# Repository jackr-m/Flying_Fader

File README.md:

# Flying Faders
## Use Rust Embassy framework to integrate 5 "flying faders" (motorized linear slide potentiometers) as a USB MIDI CC controller

- [Flying Faders](#flying-faders)
   * [Use Rust Embassy framework to integrate 5 "flying faders" (motorized linear slide potentiometers) as a USB MIDI CC controller](#use-rust-embassy-framework-to-integrate-5-flying-faders-motorized-linear-slide-potentiometers-as-a-usb-midi-cc-controller)
   * [Project Overview](#project-overview)
      + [Code](#code)
      + [Mechanical](#mechanical)

## Project Overview
Use 5 motorized linear slide potentiometers (ALPS SM10002NKA1X-HW1, sold as Adafruit P/N 5466) with a STM32H7 microprocessor programmed using the Rust Embassy framework & HAL.
There is a custom PCB for this project, with the KiCad source in the /CAD directory.

### Code
Using the Rust Embassy framework and embassy_stm32 HAL, this has been coded using an asynchronous architecture and should be very portable to nearly any STM32 variant (especially if the screen is not needed).
Code documentation located at: https://jackr-m.github.io/Flying_Fader/flying_fader/

### Mechanical
The casement is 3D printed, and STEP files are provided in the /CAD directory.
In addition, the original Onshape document is available for use or modification at [Onshape](https://cad.onshape.com/documents/5790ae0e6f82956a005dc546/w/d37346e9ef2c1592c912aa6b/e/dacfcc9dc0c38682bf8baa7f?renderMode=0&uiState=666d3492034c5f73c5a59cf9).

Faders:

https://www.adafruit.com/product/5466

Screen:

https://www.adafruit.com/product/5805

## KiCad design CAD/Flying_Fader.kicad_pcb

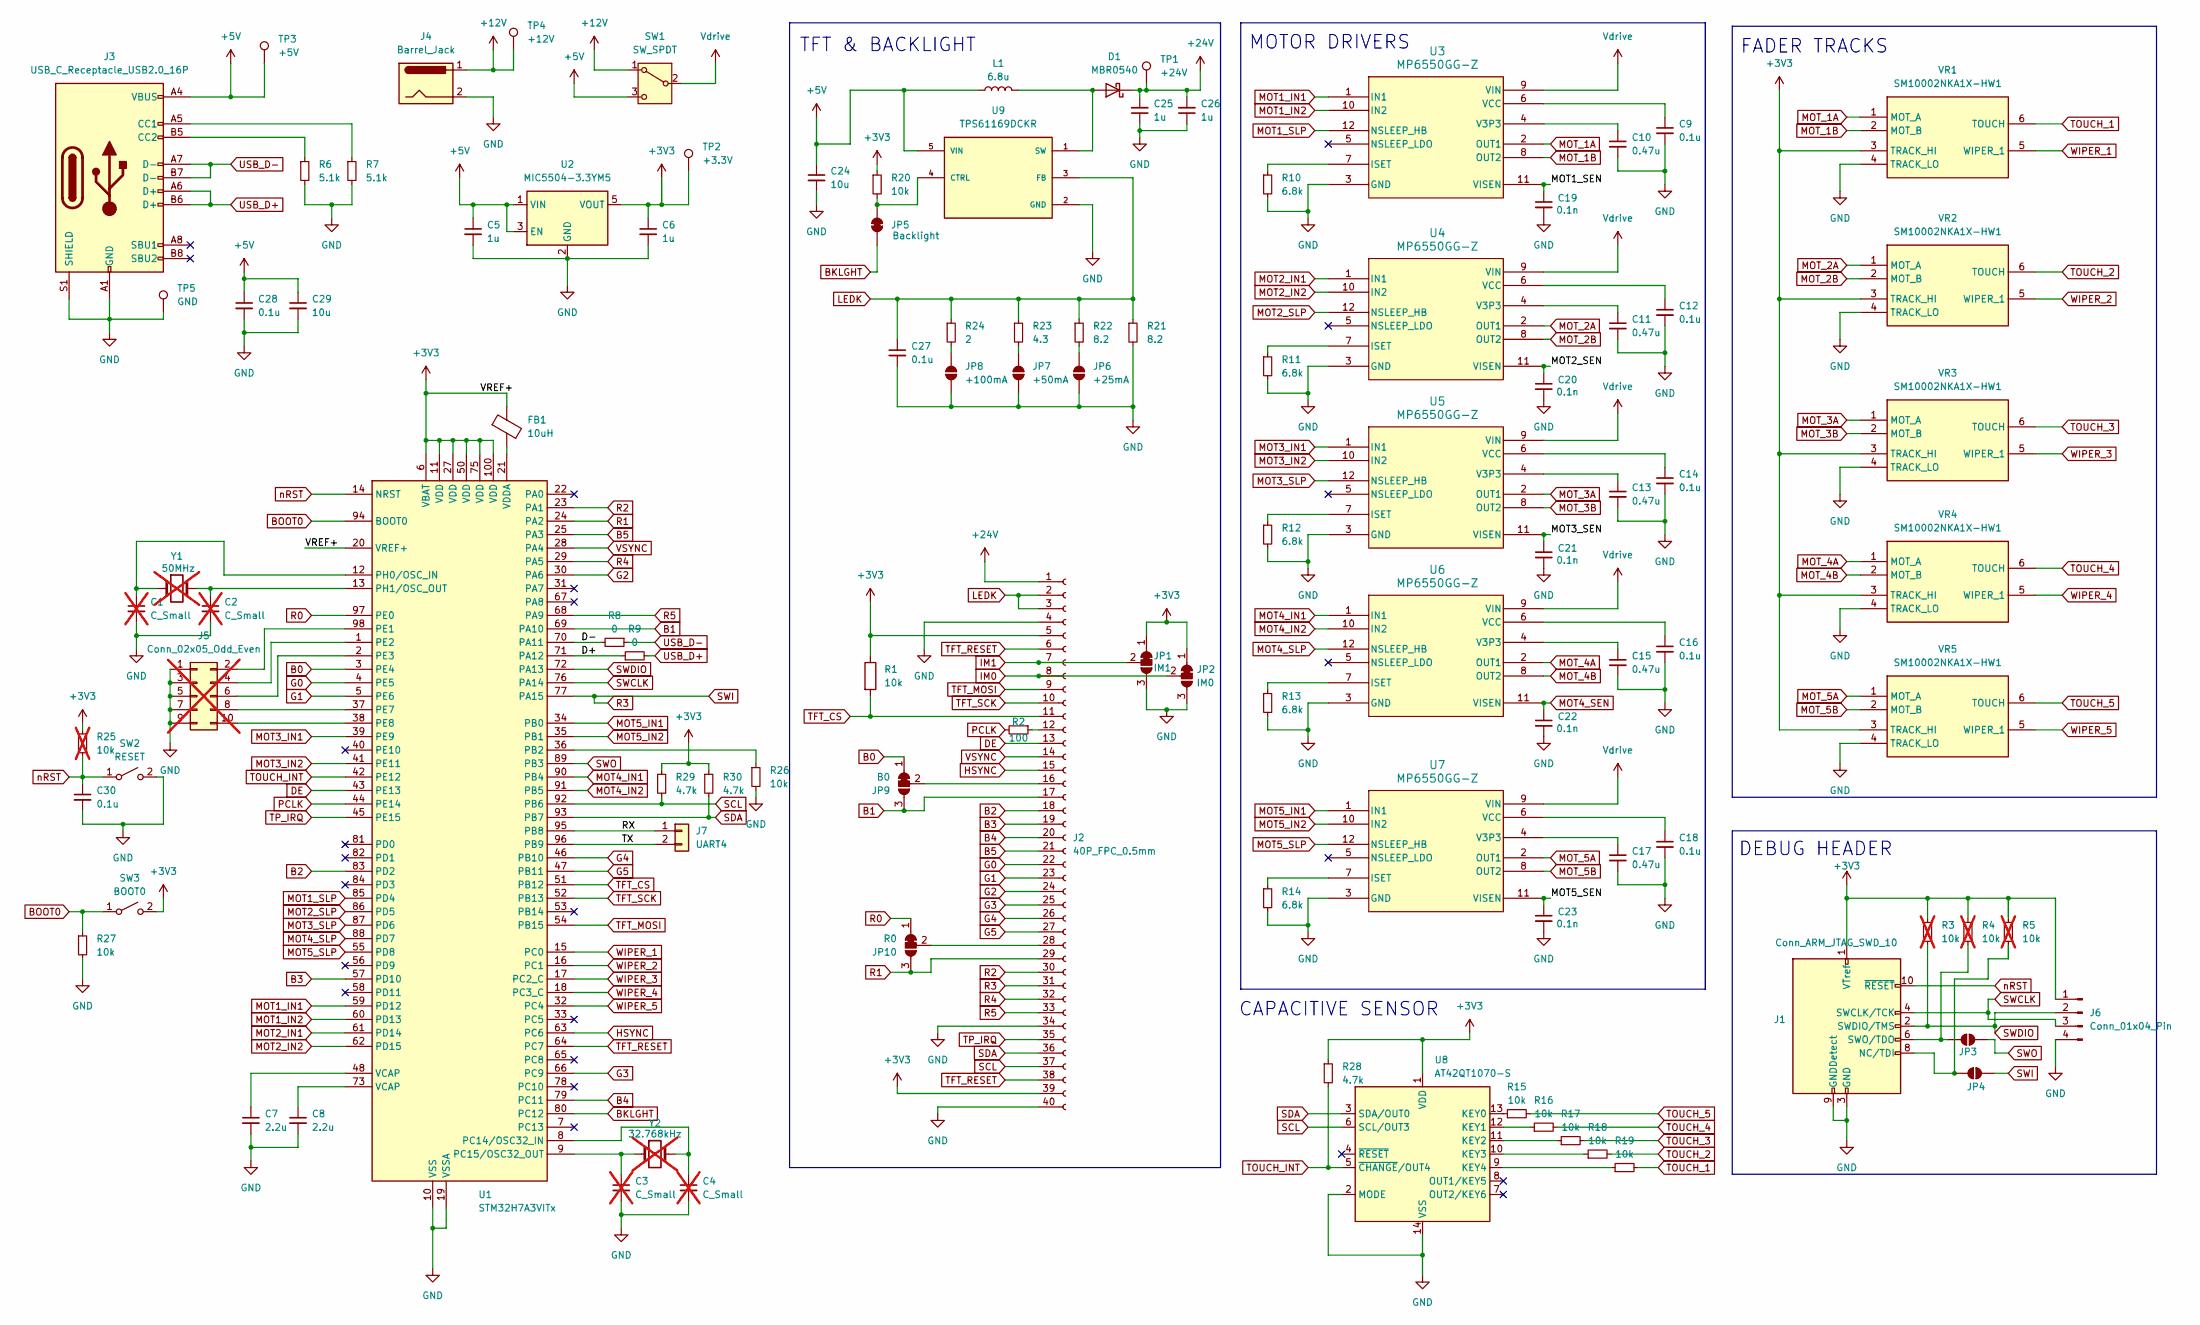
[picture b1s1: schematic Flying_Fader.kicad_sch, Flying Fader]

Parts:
C1, C2, C3, C4: C_Small; C_0805_2012Metric; not fitted
C5, C6, C25, C26: 1u; C_0805_2012Metric
C7, C8: 2.2u; C_0805_2012Metric
C9, C12, C14, C16, C18, C27, C28, C30: 0.1u; C_0805_2012Metric
C10, C11, C13, C15, C17: 0.47u; C_0805_2012Metric
C19, C20, C21, C22, C23: 0.1n; C_0805_2012Metric
C24, C29: 10u; C_0805_2012Metric
D1: MBR0540; D_SOD-123
FB1: 10uH; L_0805_2012Metric
J1: Conn_ARM_JTAG_SWD_10; PinHeader_2x05_P1.27mm_Vertical_SMD
J2: 40P_FPC_0.5mm; Omron_XF2M-4015-1A_1x40-1MP_P0.5mm_Horizontal
J3: USB_C_Receptacle_USB2.0_16P; USB_C_Receptacle_GCT_USB4085
J4: Barrel_Jack; BarrelJack_CUI_PJ-063AH_Horizontal
J5: Conn_02x05_Odd_Even; PinHeader_2x05_P2.54mm_Vertical; not fitted
J6: Conn_01x04_Pin; PinHeader_1x04_P2.54mm_Vertical
J7: UART4; PinHeader_1x02_P2.54mm_Vertical
JP1: IM1; SolderJumper-3_P1.3mm_Bridged12_Pad1.0x1.5mm_NumberLabels
JP2: IM0; SolderJumper-3_P1.3mm_Bridged12_Pad1.0x1.5mm_NumberLabels
JP3: SWO; SolderJumper-2_P1.3mm_Open_TrianglePad1.0x1.5mm
JP4: SWI; SolderJumper-2_P1.3mm_Open_TrianglePad1.0x1.5mm
JP5: Backlight; SolderJumper-2_P1.3mm_Bridged_Pad1.0x1.5mm
JP6: +25mA; SolderJumper-2_P1.3mm_Open_TrianglePad1.0x1.5mm
JP7: +50mA; SolderJumper-2_P1.3mm_Open_TrianglePad1.0x1.5mm
JP8: +100mA; SolderJumper-2_P1.3mm_Open_TrianglePad1.0x1.5mm
JP9: B0; SolderJumper-3_P1.3mm_Bridged12_Pad1.0x1.5mm_NumberLabels
JP10: R0; SolderJumper-3_P1.3mm_Bridged12_Pad1.0x1.5mm_NumberLabels
L1: 6.8u; L_0805_2012Metric
R1, R15, R16, R17, R18, R19, R20, R26, R27: 10k; R_0805_2012Metric
R2: 100; R_0805_2012Metric
R3, R4, R5, R25: 10k; R_0805_2012Metric; not fitted
R6, R7: 5.1k; R_0805_2012Metric
R8, R9: 0; R_0805_2012Metric
R10, R11, R12, R13, R14: 6.8k; R_0805_2012Metric
R21, R22: 8.2; R_0805_2012Metric
R23: 4.3; R_0805_2012Metric
R24: 2; R_0805_2012Metric
R28, R29, R30: 4.7k; R_0805_2012Metric
SW1: SW_SPDT; SW_SPDT_CK_JS102011SAQN
SW2: RESET; SW_Push_SPST_NO_Alps_SKRK
SW3: BOOT0; SW_Push_SPST_NO_Alps_SKRK
TP1: +24V; TestPoint_Pad_D1.0mm
TP2: +3.3V; TestPoint_Pad_D1.0mm
TP3: +5V; TestPoint_Pad_D1.0mm
TP4: +12V; TestPoint_Pad_D1.0mm
TP5: GND; TestPoint_Pad_D1.0mm
U1: STM32H7A3VITx; LQFP-100_14x14mm_P0.5mm
U2: MIC5504-3.3YM5; SOT-23-5
U3, U4, U5, U6, U7: MP6550GG-Z; LQFN-12-1EP_2x2mm_P0.5mm_EP0.7x0.7mm
U8: AT42QT1070-S; SOIC-14_3.9x8.7mm_P1.27mm
U9: TPS61169DCKR; SOT-353_SC-70-5; PARTREV A
VR1, VR2, VR3, VR4, VR5: SM10002NKA1X-HW1; PinHeader_1x06_P2.54mm_Vertical; Manufacturer_Part_Number SM10002NKA1X-HW1
Y1: 50MHz; Crystal_SMD_5032-2Pin_5.0x3.2mm; not fitted
Y2: 32.768kHz; Crystal_SMD_3215-2Pin_3.2x1.5mm; not fitted

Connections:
+3V3: C6.1, FB1.1, J1.1 (VTref), J2.5, J2.39, J6.1, JP1.1 (A), JP2.1 (A), R1.1, R3.1, R4.1, R5.1, R20.1, R25.1, R28.1, R29.1, R30.1, SW3.2 (B), TP2.1, U1.6 (VBAT), U1.11 (VDD), U1.20 (VREF+), U1.27 (VDD), U1.50 (VDD), U1.75 (VDD), U1.100 (VDD), U2.5 (VOUT), U8.1 (VDD), VR1.3 (TRACK_HI), VR2.3 (TRACK_HI), VR3.3 (TRACK_HI), VR4.3 (TRACK_HI), VR5.3 (TRACK_HI)
+5V: C5.1, C24.1, C28.1, C29.1, J3.A4 (VBUS), J3.A9 (VBUS), J3.B4 (VBUS), J3.B9 (VBUS), L1.1, SW1.3 (C), TP3.1, U2.1 (VIN), U2.3 (EN), U9.5 (VIN)
+12V: J4.1, SW1.1 (A), TP4.1
+24V: C25.2, C26.2, D1.1 (K), J2.1, TP1.1
/D+: R9.1, U1.71 (PA12)
/D-: R8.2, U1.70 (PA11)
/MOT1_SEN: C19.1, U3.11 (VISEN)
/MOT2_SEN: C20.1, U4.11 (VISEN)
/MOT3_SEN: C21.1, U5.11 (VISEN)
/MOT5_SEN: C23.1, U7.11 (VISEN)
/RX: J7.1, U1.95 (PB8)
/TX: J7.2, U1.96 (PB9)
B0: JP9.1 (A), U1.3 (PE4)
B1: J2.17, JP9.3 (B), U1.69 (PA10)
B2: J2.18, U1.83 (PD2)
B3: J2.19, U1.57 (PD10)
B4: J2.20, U1.79 (PC11)
B5: J2.21, U1.25 (PA3)
BKLGHT: JP5.1 (A), U1.80 (PC12)
BOOT0: R27.1, SW3.1 (A), U1.94 (BOOT0)
DE: J2.13, U1.43 (PE13)
G0: J2.22, U1.4 (PE5)
G1: J2.23, U1.5 (PE6)
G2: J2.24, U1.30 (PA6)
G3: J2.25, U1.66 (PC9)
G4: J2.26, U1.46 (PB10)
G5: J2.27, U1.47 (PB11)
GND: C1.2, C2.2, C3.2, C4.2, C5.2, C6.2, C7.2, C8.2, C9.2, C10.2, C11.2, C12.2, C13.2, C14.2, C15.2, C16.2, C17.2, C18.2, C19.2, C20.2, C21.2, C22.2, C23.2, C24.2, C25.1, C26.1, C27.2, C28.2, C29.2, C30.2, J1.3 (GND), J1.5 (GND), J1.9 (GNDDetect), J2.4, J2.34, J2.40, J3.A1 (GND), J3.A12 (GND), J3.B1 (GND), J3.B12 (GND), J3.S1 (SHIELD), J4.2, J5.1, J5.3, J5.5, J5.7, J5.9, J6.4, JP1.3 (B), JP2.3 (B), JP6.1 (A), JP7.1 (A), JP8.1 (A), R6.2, R7.2, R10.2, R11.2, R12.2, R13.2, R14.2, R21.2, R26.2, R27.2, SW2.2 (B), TP5.1, U1.10 (VSS), U1.19 (VSSA), U1.26 (VSS), U1.49 (VSS), U1.74 (VSS), U1.99 (VSS), U2.2 (GND), U3.3 (GND), U4.3 (GND), U5.3 (GND), U6.3 (GND), U7.3 (GND), U8.2 (MODE), U8.14 (VSS), U9.2 (GND), VR1.4 (TRACK_LO), VR2.4 (TRACK_LO), VR3.4 (TRACK_LO), VR4.4 (TRACK_LO), VR5.4 (TRACK_LO)
HSYNC: J2.15, U1.63 (PC6)
IM0: J2.8, JP2.2 (C)
IM1: J2.7, JP1.2 (C)
LEDK: C27.1, J2.2, J2.3, R21.1, R22.1, R23.1, R24.1, U9.3 (FB)
MOT1_IN1: U1.59 (PD12), U3.1 (IN1)
MOT1_IN2: U1.60 (PD13), U3.10 (IN2)
MOT1_SLP: U1.85 (PD4), U3.12 (NSLEEP_HB)
MOT2_IN1: U1.61 (PD14), U4.1 (IN1)
MOT2_IN2: U1.62 (PD15), U4.10 (IN2)
MOT2_SLP: U1.86 (PD5), U4.12 (NSLEEP_HB)
MOT3_IN1: U1.39 (PE9), U5.1 (IN1)
MOT3_IN2: U1.41 (PE11), U5.10 (IN2)
MOT3_SLP: U1.87 (PD6), U5.12 (NSLEEP_HB)
MOT4_IN1: U1.90 (PB4), U6.1 (IN1)
MOT4_IN2: U1.91 (PB5), U6.10 (IN2)
MOT4_SEN: C22.1, U6.11 (VISEN)
MOT4_SLP: U1.88 (PD7), U6.12 (NSLEEP_HB)
MOT5_IN1: U1.34 (PB0), U7.1 (IN1)
MOT5_IN2: U1.35 (PB1), U7.10 (IN2)
MOT5_SLP: U1.55 (PD8), U7.12 (NSLEEP_HB)
MOT_1A: U3.2 (OUT1), VR1.1 (MOT_A)
MOT_1B: U3.8 (OUT2), VR1.2 (MOT_B)
MOT_2A: U4.2 (OUT1), VR2.1 (MOT_A)
MOT_2B: U4.8 (OUT2), VR2.2 (MOT_B)
MOT_3A: U5.2 (OUT1), VR3.1 (MOT_A)
MOT_3B: U5.8 (OUT2), VR3.2 (MOT_B)
MOT_4A: U6.2 (OUT1), VR4.1 (MOT_A)
MOT_4B: U6.8 (OUT2), VR4.2 (MOT_B)
MOT_5A: U7.2 (OUT1), VR5.1 (MOT_A)
MOT_5B: U7.8 (OUT2), VR5.2 (MOT_B)
unnamed: C7.1, U1.48 (VCAP)
unnamed: C8.1, U1.73 (VCAP)
unnamed: D1.2 (A), L1.2, U9.1 (SW)
unnamed: J1.8 (NC/TDI), JP4.1 (A), R5.2
unnamed: J1.6 (SWO/TDO), JP3.1 (A), R4.2
unnamed: J2.12, R2.1
unnamed: J2.16, JP9.2 (C)
unnamed: J2.28, JP10.2 (C)
unnamed: J3.A5 (CC1), R7.1
unnamed: J3.B5 (CC2), R6.1
unnamed: J5.2, U1.98 (PE1)
unnamed: J5.4, U1.1 (PE2)
unnamed: J5.6, U1.2 (PE3)
unnamed: J5.8, U1.37 (PE7)
unnamed: J5.10, U1.38 (PE8)
unnamed: JP5.2 (B), R20.2, U9.4 (CTRL)
unnamed: JP6.2 (B), R22.2
unnamed: JP7.2 (B), R23.2
unnamed: JP8.2 (B), R24.2
unnamed: R26.1, U1.36 (PB2)
unnamed: C4.1, U1.8 (PC14/OSC32_IN), Y2.2
unnamed: C3.1, U1.9 (PC15/OSC32_OUT), Y2.1
unnamed: C1.1, U1.12 (PH0/OSC_IN), Y1.1
unnamed: C2.1, U1.13 (PH1/OSC_OUT), Y1.2
unnamed: FB1.2, U1.21 (VDDA)
unnamed: R10.1, U3.7 (ISET)
unnamed: C10.1, U3.4 (V3P3)
unnamed: C9.1, U3.6 (VCC)
unnamed: R11.1, U4.7 (ISET)
unnamed: C11.1, U4.4 (V3P3)
unnamed: C12.1, U4.6 (VCC)
unnamed: R12.1, U5.7 (ISET)
unnamed: C13.1, U5.4 (V3P3)
unnamed: C14.1, U5.6 (VCC)
unnamed: R13.1, U6.7 (ISET)
unnamed: C15.1, U6.4 (V3P3)
unnamed: C16.1, U6.6 (VCC)
unnamed: R14.1, U7.7 (ISET)
unnamed: C17.1, U7.4 (V3P3)
unnamed: C18.1, U7.6 (VCC)
unnamed: R15.1, U8.13 (KEY0)
unnamed: R16.1, U8.12 (KEY1)
unnamed: R17.1, U8.11 (KEY2)
unnamed: R18.1, U8.10 (KEY3)
unnamed: R19.1, U8.9 (KEY4)
PCLK: R2.2, U1.44 (PE14)
R0: JP10.1 (A), U1.97 (PE0)
R1: J2.29, JP10.3 (B), U1.24 (PA2)
R2: J2.30, U1.23 (PA1)
R3: J2.31, JP4.2 (B), U1.77 (PA15)
R4: J2.32, U1.29 (PA5)
R5: J2.33, U1.68 (PA9)
SCL: J2.37, R29.2, U1.92 (PB6), U8.6 (SCL/OUT3)
SDA: J2.36, R30.2, U1.93 (PB7), U8.3 (SDA/OUT0)
SWCLK: J1.4 (SWCLK/TCK), J6.3, U1.76 (PA14)
SWDIO: J1.2 (SWDIO/TMS), J6.2, R3.2, U1.72 (PA13)
SWO: JP3.2 (B), U1.89 (PB3)
TFT_CS: J2.11, R1.2, U1.51 (PB12)
TFT_MOSI: J2.9, U1.54 (PB15)
TFT_RESET: J2.6, J2.38, U1.64 (PC7)
TFT_SCK: J2.10, U1.52 (PB13)
TOUCH_1: R19.2, VR1.6 (TOUCH)
TOUCH_2: R18.2, VR2.6 (TOUCH)
TOUCH_3: R17.2, VR3.6 (TOUCH)
TOUCH_4: R16.2, VR4.6 (TOUCH)
TOUCH_5: R15.2, VR5.6 (TOUCH)
TOUCH_INT: R28.2, U1.42 (PE12), U8.5 (~CHANGE/OUT4)
TP_IRQ: J2.35, U1.45 (PE15)
USB_D+: J3.A6 (D+), J3.B6 (D+), R9.2
USB_D-: J3.A7 (D-), J3.B7 (D-), R8.1
VSYNC: J2.14, U1.28 (PA4)
Vdrive: SW1.2 (B), U3.9 (VIN), U4.9 (VIN), U5.9 (VIN), U6.9 (VIN), U7.9 (VIN)
WIPER_1: U1.15 (PC0), VR1.5 (WIPER_1)
WIPER_2: U1.16 (PC1), VR2.5 (WIPER_1)
WIPER_3: U1.17 (PC2_C), VR3.5 (WIPER_1)
WIPER_4: U1.18 (PC3_C), VR4.5 (WIPER_1)
WIPER_5: U1.32 (PC4), VR5.5 (WIPER_1)
nRST: C30.1, J1.10 (~RESET), R25.2, SW2.1 (A), U1.14 (NRST)

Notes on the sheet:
DEBUG HEADER
CAPACITIVE SENSOR
MOTOR DRIVERS
TFT & BACKLIGHT
FADER TRACKS

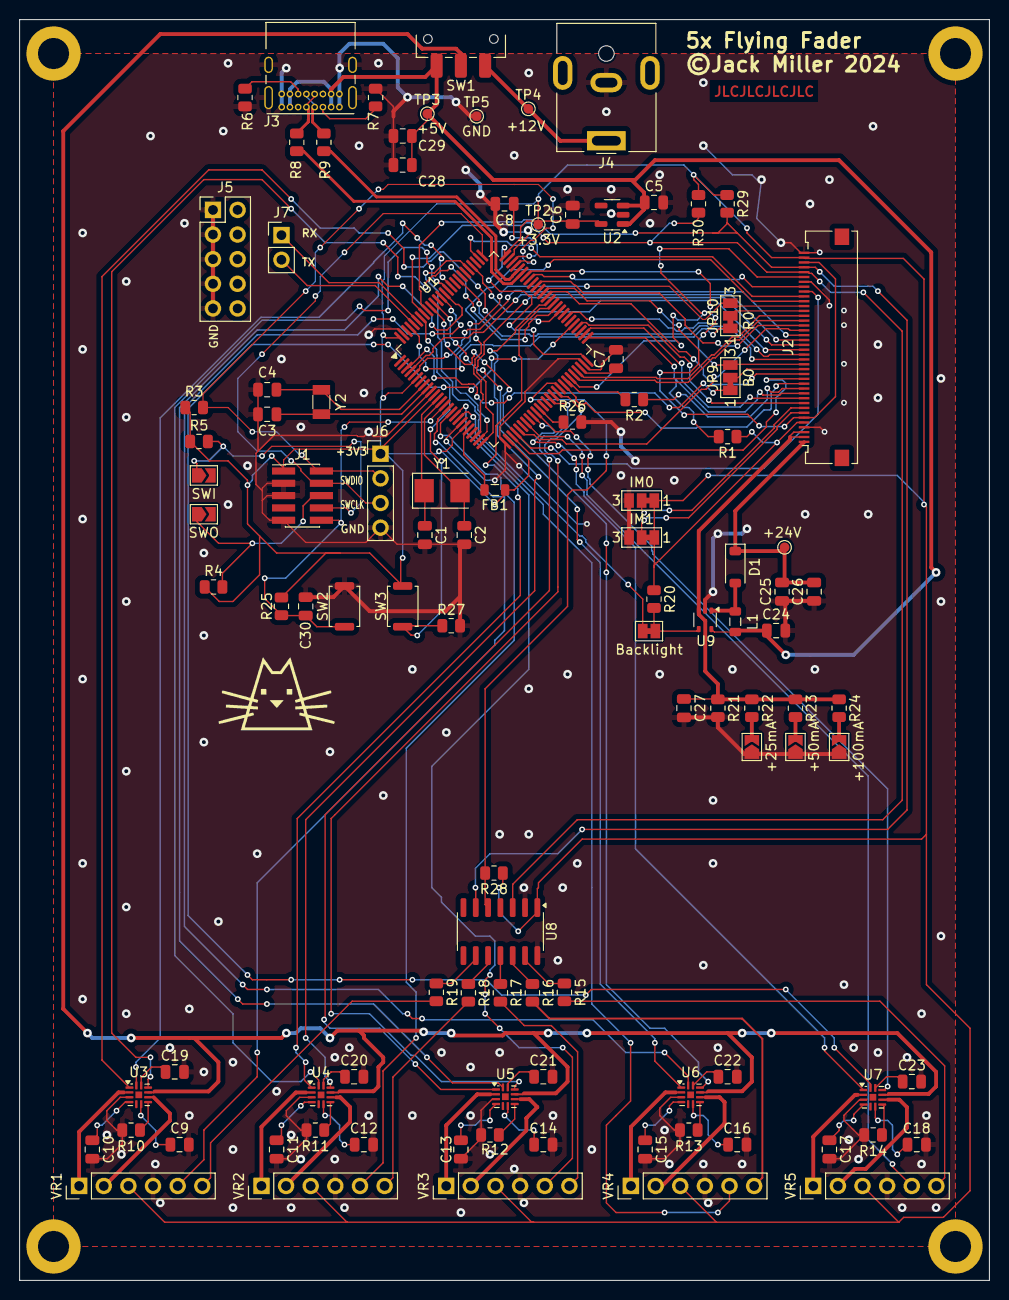
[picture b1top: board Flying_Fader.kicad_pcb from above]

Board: 2 copper layers, 100.0 x 130.0 mm, 104 parts (0 on the bottom side), 136 nets.

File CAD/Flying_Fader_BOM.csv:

"Reference","Value","Datasheet","Footprint","Qty","DNP"
"C1,C2,C3,C4","C_Small","~","Capacitor_SMD:C_0805_2012Metric","4","DNP"
"C5,C6,C25,C26","1u","~","Capacitor_SMD:C_0805_2012Metric","4",""
"C7,C8","2.2u","~","Capacitor_SMD:C_0805_2012Metric","2",""
"C9,C12,C14,C16,C18,C27,C28,C30","0.1u","~","Capacitor_SMD:C_0805_2012Metric","8",""
"C10,C11,C13,C15,C17","0.47u","~","Capacitor_SMD:C_0805_2012Metric","5",""
"C19,C20,C21,C22,C23","0.1n","~","Capacitor_SMD:C_0805_2012Metric","5",""
"C24,C29","10u","~","Capacitor_SMD:C_0805_2012Metric","2",""
"D1","MBR0540","http://www.mccsemi.com/up_pdf/MBR0520~MBR0580(SOD123).pdf","Diode_SMD:D_SOD-123","1",""
"FB1","10uH","~","Inductor_SMD:L_0805_2012Metric","1",""
"J1","Conn_ARM_JTAG_SWD_10","http://infocenter.arm.com/help/topic/com.arm.doc.ddi0314h/DD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","Connector_PinHeader_1.27mm:PinHeader_2x05_P1.27mm_Vertical_SMD","1",""
"J2","40P_FPC_0.5mm","~","Connector_FFC-FPC:Omron_XF2M-4015-1A_1x40-1MP_P0.5mm_Horizontal","1",""
"J3","USB_C_Receptacle_USB2.0_16P","https://www.usb.org/sites/default/files/documents/usb_type-c.zip","Connector_USB:USB_C_Receptacle_GCT_USB4085","1",""
"J4","Barrel_Jack","~","Connector_BarrelJack:BarrelJack_CUI_PJ-063AH_Horizontal","1",""
"J5","Conn_02x05_Odd_Even","~","Connector_PinHeader_2.54mm:PinHeader_2x05_P2.54mm_Vertical","1",""
"J6","Conn_01x04_Pin","~","Connector_PinHeader_2.54mm:PinHeader_1x04_P2.54mm_Vertical","1",""
"J7","UART4","~","Connector_PinHeader_2.54mm:PinHeader_1x02_P2.54mm_Vertical","1",""
"L1","6.8u","~","Inductor_SMD:L_0805_2012Metric","1",""
"R1,R15,R16,R17,R18,R19,R20,R26,R27","10k","~","Resistor_SMD:R_0805_2012Metric","9",""
"R2","100","~","Resistor_SMD:R_0805_2012Metric","1",""
"R3,R4,R5,R25","10k","~","Resistor_SMD:R_0805_2012Metric","4","DNP"
"R6,R7","5.1k","~","Resistor_SMD:R_0805_2012Metric","2",""
"R8,R9","0","~","Resistor_SMD:R_0805_2012Metric","2",""
"R10,R11,R12,R13,R14","6.8k","~","Resistor_SMD:R_0805_2012Metric","5",""
"R21,R22","8.2","~","Resistor_SMD:R_0805_2012Metric","2",""
"R23","4.3","~","Resistor_SMD:R_0805_2012Metric","1",""
"R24","2","~","Resistor_SMD:R_0805_2012Metric","1",""
"R28,R29,R30","4.7k","~","Resistor_SMD:R_0805_2012Metric","3",""
"SW1","SW_SPDT","~","Button_Switch_SMD:SW_SPDT_CK_JS102011SAQN","1",""
"SW2","RESET","~","Button_Switch_SMD:SW_Push_SPST_NO_Alps_SKRK","1",""
"SW3","BOOT0","~","Button_Switch_SMD:SW_Push_SPST_NO_Alps_SKRK","1",""
"TP1","+24V","~","TestPoint:TestPoint_Pad_D1.0mm","1",""
"TP2","+3.3V","~","TestPoint:TestPoint_Pad_D1.0mm","1",""
"TP3","+5V","~","TestPoint:TestPoint_Pad_D1.0mm","1",""
"TP4","+12V","~","TestPoint:TestPoint_Pad_D1.0mm","1",""
"TP5","GND","~","TestPoint:TestPoint_Pad_D1.0mm","1",""
"U1","STM32H7A3VITx","https://www.st.com/resource/en/datasheet/stm32h7a3vi.pdf","Package_QFP:LQFP-100_14x14mm_P0.5mm","1",""
"U2","MIC5504-3.3YM5","http://ww1.microchip.com/downloads/en/DeviceDoc/MIC550X.pdf","Package_TO_SOT_SMD:SOT-23-5","1",""
"U3,U4,U5,U6,U7","MP6550GG-Z","MP6550GG-Z","Package_DFN_QFN:LQFN-12-1EP_2x2mm_P0.5mm_EP0.7x0.7mm","5",""
"U8","AT42QT1070-S","http://ww1.microchip.com/downloads/en/DeviceDoc/Atmel-9596-A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","Package_SO:SOIC-14_3.9x8.7mm_P1.27mm","1",""
"U9","TPS61169DCKR","","Package_TO_SOT_SMD:SOT-353_SC-70-5","1",""
"VR1,VR2,VR3,VR4,VR5","SM10002NKA1X-HW1","https://cdn-shop.adafruit.com/product-files/5466/5466_datash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","Connector_PinHeader_2.54mm:PinHeader_1x06_P2.54mm_Vertical","5",""
"Y1","50MHz","~","Crystal:Crystal_SMD_5032-2Pin_5.0x3.2mm","1","DNP"
"Y2","32.768kHz","~","Crystal:Crystal_SMD_3215-2Pin_3.2x1.5mm","1","DNP"

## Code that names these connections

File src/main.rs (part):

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    i2c_config.frequency = Hertz(100_000);
    let mut i2c = I2c::new(
        p.I2C1,
        p.PB6,
        p.PB7,
        Irqs,
        p.DMA1_CH4,
        p.DMA1_CH5,
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    }

    // LCD initialization
    let lcd_backlight = p.PC12;
    let lcd_backlight_channel = PwmPin::new(lcd_backlight, OutputType::PushPull);
    let mut lcd_backlight_pwm = SimplePwm::new(p.TIM15, Some(lcd_backlight_channel), None, None, None, khz(50), Default::default());

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    lcd_backlight_pwm.ch1().set_duty_cycle_percent(backlight_duty);
    
    // Motor initialization
    let mot1_sleep = p.PD4;
    let mot1_in1 = p.PD12;
    let mot1_in2 = p.PD13;
    let mot2_sleep = p.PD5;
    let mot2_in1 = p.PD14;
    let mot2_in2 = p.PD15;
    let mot3_sleep = p.PD6;
    let mot3_in1 = p.PE9;
    let mot3_in2 = p.PE11;
    let mot4_sleep = p.PD7;
    let mot4_in1 = p.PB4;
    let mot4_in2 = p.PB5;
    let mot5_sleep = p.PD8;
    let mot5_in1 = p.PB0;
    let mot5_in2 = p.PB1;

    let mut sleep1 = Output::new(mot1_sleep, Level::High, Speed::Low);
    let mut sleep2 = Output::new(mot2_sleep, Level::High, Speed::Low);
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    sleep4.set_high();
    sleep5.set_high();

    let mot1_ch1 = PwmPin::new(mot1_in1, OutputType::PushPull);
    let mot1_ch2 = PwmPin::new(mot1_in2, OutputType::PushPull);
    let mut mot1_pwm = SimplePwm::new(p.TIM4, Some(mot1_ch1), Some(mot1_ch2), None, None, khz(20), Default::default());
    let mot2_ch1 = PwmPin::new(mot2_in1, OutputType::PushPull);
    let mot2_ch2 = PwmPin::new(mot2_in2, OutputType::PushPull);
    let mut mot2_pwm = SimplePwm::new(unsafe {TIM4::steal()}, None, None, Some(mot2_ch1), Some(mot2_ch2), khz(20), Default::default());
    let mot3_ch1 = PwmPin::new(mot3_in1, OutputType::PushPull);
    let mot3_ch2 = PwmPin::new(mot3_in2, OutputType::PushPull);
    let mut mot3_pwm = SimplePwm::new(p.TIM1, Some(mot3_ch1), Some(mot3_ch2), None, None, khz(20), Default::default());
    let mot4_ch1 = PwmPin::new(mot4_in1, OutputType::PushPull);
    let mot4_ch2 = PwmPin::new(mot4_in2, OutputType::PushPull);
    let mut mot4_pwm = SimplePwm::new(p.TIM3, Some(mot4_ch1), Some(mot4_ch2), None, None, khz(20), Default::default());
    let mot5_ch1 = PwmPin::new(mot5_in1, OutputType::PushPull);
    let mot5_ch2 = PwmPin::new(mot5_in2, OutputType::PushPull);
    let mut mot5_pwm = SimplePwm::new(unsafe {TIM3::steal()}, None, None, Some(mot5_ch1), Some(mot5_ch2), khz(20), Default::default());

    mot1_pwm.ch1().set_polarity(OutputPolarity::ActiveLow); // inverted PWM
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    let mut ep_out_buffer = [0u8; 256];
    let mut config = usb::Config::default();
    config.vbus_detection = false; // Necessary since STM32 is powered solely by USB
    let driver = Driver::new_fs(p.USB_OTG_HS, Irqs, p.PA12, p.PA11, &mut ep_out_buffer, config);
    // Create embassy-usb Config
    let mut config = embassy_usb::Config::new(0xc0de, 0xcafe);
    config.manufacturer = Some("CollapseOfSound");
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
    let slider_fut = async {
        loop {
            let mot1_measured = adc2.blocking_read(&mut p.PC0) >> 1;
            let mot2_measured = adc2.blocking_read(&mut p.PC1) >> 1;// was adc2.read
            let mot3_measured = adc2.blocking_read(&mut p.PC2_C) >> 1;
            let mot4_measured = adc2.blocking_read(&mut p.PC3_C) >> 1;
            let mot5_measured = adc2.blocking_read(&mut p.PC4) >> 1;
            // info!("measured: {}, {}, {}, {}, {}", mot1_measured, mot2_measured, mot3_measured, mot4_measured, mot5_measured);
            
            SLIDER_1_MEAS.store(mot1_measured, Ordering::Relaxed);
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
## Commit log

2024-06-10 Update embassy dependencies to most recent main branch commit
2024-06-10 Revert embassy versions, enable P2_C and P3_C
2024-06-11 Enable all 5 faders
2024-06-11 Correct capacitive touch sensitivity
2024-06-14 Enable LCD backlight dimming
2024-06-14 Add documentation
2024-06-14 Update .gitignore to include generated doc files
2024-06-14 Add documentation files
2024-06-14 Fix docs directory
2024-06-14 Add CAD files (PCB & 3D)
2024-06-15 Create wjh
2024-06-15 Add photos for README
2024-06-15 Add final product photo
2024-06-15 Add CAD photo
2024-06-15 Add a sample song using Ableton Live
2025-11-30 Updated dependencies for latest embassy and rust 2024
2025-11-30 Remove old documentation from dependencies
2025-12-01 Alterations to code to get it to compile with new embassy major version. Untested
2025-12-07 Adding IDE run configurations
2025-12-07 Fully updated & tested for latest embassy-rs

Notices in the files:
CAD/Flying_Fader.kicad_pcb:
©Jack Miller 2024
